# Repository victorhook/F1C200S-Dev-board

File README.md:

# F1C200S Dev Board

Custom PCB with the Allwinner F1C200S SoC, built to learn more about embedded Linux!

## Overview

The F1C200S is an ARM9 (ARM926EJ-S) processor with 64MB DDR1 RAM built into the package.
No external memory needed -- a 2-layer PCB is all it takes to run Linux.

## Features

- **SoC**: Allwinner F1C200S (ARM9 @ 408MHz, 64MB SiP DDR1)
- **Boot**: Micro SD card
- **USB**: USB-C (OTG + FEL mode flashing)
- **Debug**: UART0 console header, RESET and BOOT/FEL buttons
- **Power**: 5V USB input, 3x LDO regulators (3.3V, 2.5V, 1.2V)
- **Clock**: 24MHz crystal

## Broken-out peripherals

The board exposes most of the SoC's peripherals via pin headers:

- 3x UART, 3x I2C (TWI), 2x SPI, 2x PWM
- 8-bit parallel camera interface (CSI) on a 2x9 header for OV2640 breakout
- Composite video output (TVOUT)
- Built-in audio codec (headphone out, mic in, line in, FM in)
- IR receiver input
- Two 16-pin 2.54mm headers with misc GPIO and power (Port D and Port E)

## Hardware

- **EDA**: KiCad 9
- **PCB**: 2-layer
- **Assembly**: Designed for JLCPCB SMT assembly

Schematic and board files are in `F1C200S-Dev-board/`.

## Software

The `br2-external/` tree has everything needed to build a bootable SD card image with Buildroot:

- **Linux**: 6.19.11 (suniv/sun8i, custom device tree)
- **U-Boot**: 2025.01 (`licheepi_nano` defconfig + custom DTS)
- **Rootfs**: musl + BusyBox, Dropbear SSH, wpa_supplicant
- **Flashing**: `sunxi-fel` over USB

```sh
make            # clone buildroot + build everything
make kernel     # safe kernel rebuild after DTS / linux patch / fragment changes
make uboot      # safe U-Boot rebuild after U-Boot DTS / patch / config changes
make menuconfig # tweak buildroot config
```

Output: `buildroot/output/images/sdcard.img`

## Common workflows

Use these as the default rules of thumb:

| If you changed... | Rebuild with... | Deploy with... |
| --- | --- | --- |
| `src/**` userspace tools/apps | `make deploy-apps` | included in `make deploy-apps` |
| `br2-external/board/f1c200s-devboard/dts/**` | `make kernel` | `make deploy-kernel` |
| `br2-external/board/f1c200s-devboard/linux-patches/**` | `make kernel` | `make deploy-kernel` |
| `br2-external/board/f1c200s-devboard/linux.fragment` | `make kernel` | `make deploy-kernel` |
| kernel config via `make linux-menuconfig` | `make kernel` | `make deploy-kernel` |
| `br2-external/board/f1c200s-devboard/u-boot*` or U-Boot DTS/patches | `make uboot` | no network deploy target; reflash boot media |
| Buildroot defconfig / package selection | `make defconfig && make` | depends on what changed |

Notes:

- `make deploy-kernel` only installs `zImage` and `suniv-f1c200s-devboard.dtb`
  to the boot partition on the running board.
- `make deploy-apps` rebuilds and copies the userspace binaries under `src/`
  plus selected target tools like `yavta`.
- There is intentionally no `make image` target anymore. It was too fragile for
  kernel patch stack changes.

## Status

Rev A -- initial prototype

**2026-04-20**: First Linux boot! Rev A boards arrived and reached a busybox root shell
on UART0. The core path (USB-C power, DDR1, 24MHz PLL, MMC, pinctrl, UART, GPIO LEDs,
SPI) is all verified working under Linux 6.19.11. Later the same day, USB composite
gadget (CDC ECM ethernet + CDC ACM serial) came up — one USB-C cable now carries
power, a shell on `/dev/ttyACM0`, and a network link on `usb0` (192.168.100.1).
Buttons work via the input subsystem (`/dev/input/event0`) after a kernel patch
that aligns suniv's pinctrl strict-mode behaviour with other sunxi SoCs.

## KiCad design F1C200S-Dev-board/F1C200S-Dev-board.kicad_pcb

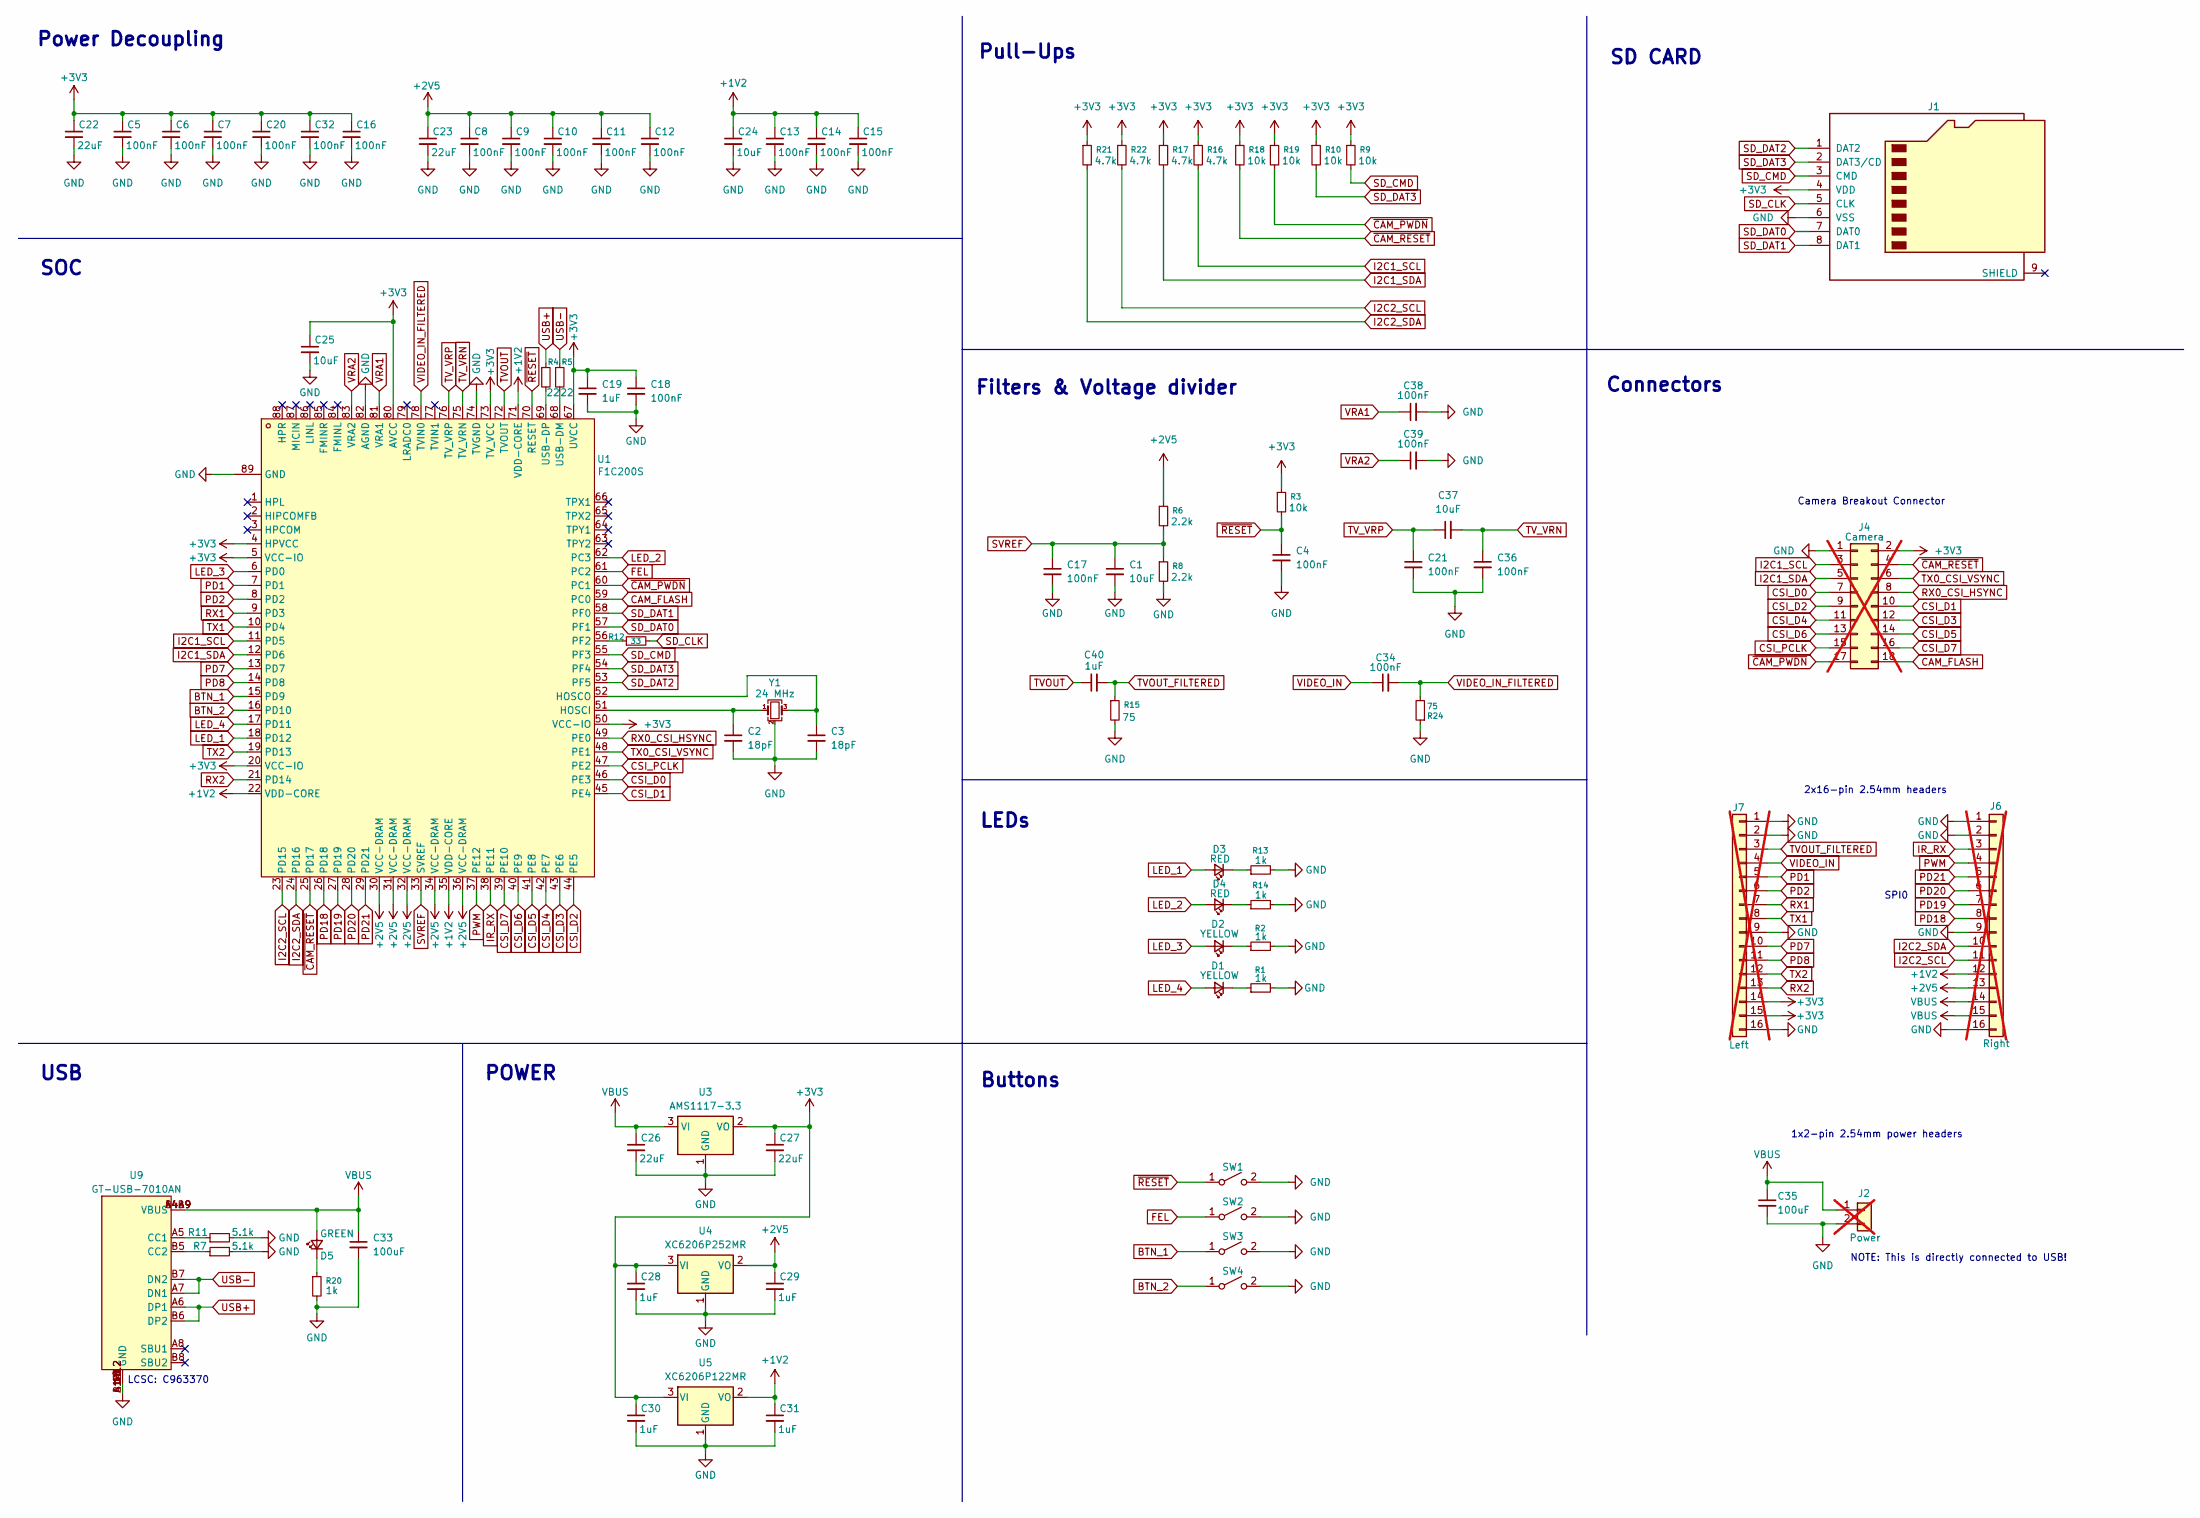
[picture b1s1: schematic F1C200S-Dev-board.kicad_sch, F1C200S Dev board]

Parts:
C1, C24, C25: 10uF; C_0603_1608Metric
C2, C3: 18pF; C_0402_1005Metric; LCSC Part C1549
C4, C5, C6, C7, C8, C9, C10, C11, C12, C13, C14, C15, C16, C17, C18, C20, C21, C32, C34, C36, C38, C39: 100nF; C_0402_1005Metric
C19, C40: 1uF; C_0402_1005Metric
C22, C23, C26, C27: 22uF; C_0603_1608Metric
C28, C29, C30, C31: 1uF; C_0603_1608Metric
C33, C35: 100uF; C_1206_3216Metric; LCSC Part C15008
C37: 10uF; C_0402_1005Metric
D1, D2: YELLOW; LED_0603_1608Metric; LCSC Part C2290
D3, D4: RED; LED_0603_1608Metric; LCSC Part C2286
D5: GREEN; LED_0805_2012Metric; LCSC Part C2297
J1: Micro_SD_Card; TF-SMD_TF-021B-H265; LCSC Part C498185
J2: Power; PinSocket_1x02_P2.54mm_Vertical; not fitted
J4: Camera; PinSocket_2x09_P2.54mm_Vertical; not fitted
J6: Right; PinSocket_1x16_P2.54mm_Vertical; not fitted
J7: Left; PinSocket_1x16_P2.54mm_Vertical; not fitted
R1, R2, R13, R14, R20: 1k; R_0402_1005Metric
R3, R9, R10, R18, R19: 10k; R_0402_1005Metric
R4, R5: 22; R_0402_1005Metric; LCSC Part C25092
R6, R8: 2.2k; R_0402_1005Metric
R7, R11: 5.1k; R_0402_1005Metric
R12: 33; R_0402_1005Metric; LCSC Part C25105
R15, R24: 75; R_0603_1608Metric; LCSC Part C4275
R16, R17, R21, R22: 4.7k; R_0402_1005Metric
SW1, SW2, SW3, SW4: SW_SPST; SW-SMD_L3.9-W3.0-P4.45; LCSC Part C720477
U1: F1C200S; QFN-88_L10.0-W10.0-P0.40-BL-EP6.75; LCSC Part C2879851
U3: AMS1117-3.3; SOT-223-3_TabPin2; LCSC Part C6186
U4: XC6206P252MR; SOT-23-3; LCSC Part C15906
U5: XC6206P122MR; SOT-23-3; LCSC Part C424699
U9: GT-USB-7010AN; USB-SMD_GT-USB-7010AN; LCSC Part C963370
Y1: 24 MHz; Crystal_SMD_3225-4Pin_3.2x2.5mm; LCSC Part C37635376

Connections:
+1V2: C13.1, C14.1, C15.1, C24.1, C31.1, J6.12, U1.22 (VDD-CORE), U1.35 (VDD-CORE), U1.71 (VDD-CORE), U5.2 (VO)
+2V5: C8.1, C9.1, C10.1, C11.1, C12.1, C23.1, C29.1, J6.13, R6.1, U1.30 (VCC-DRAM), U1.31 (VCC-DRAM), U1.32 (VCC-DRAM), U1.34 (VCC-DRAM), U1.36 (VCC-DRAM), U4.2 (VO)
+3V3: C5.1, C6.1, C7.1, C16.1, C18.1, C19.1, C20.1, C22.1, C25.1, C27.1, C28.1, C30.1, C32.1, J1.4 (VDD), J4.2, J7.14, J7.15, R3.1, R9.1, R10.1, R16.1, R17.1, R18.1, R19.1, R21.1, R22.1, U1.4 (HPVCC), U1.5 (VCC-IO), U1.20 (VCC-IO), U1.50 (VCC-IO), U1.67 (UVCC), U1.73 (TV_VCC), U1.80 (AVCC), U3.2 (VO), U4.3 (VI), U5.3 (VI)
BTN_1: SW3.1 (A), U1.15 (PD9)
BTN_2: SW4.1 (A), U1.16 (PD10)
CAM_FLASH: J4.18, U1.59 (PC0)
CSI_D0: J4.7, U1.46 (PE3)
CSI_D1: J4.10, U1.45 (PE4)
CSI_D2: J4.9, U1.44 (PE5)
CSI_D3: J4.12, U1.43 (PE6)
CSI_D4: J4.11, U1.42 (PE7)
CSI_D5: J4.14, U1.41 (PE8)
CSI_D6: J4.13, U1.40 (PE9)
CSI_D7: J4.16, U1.39 (PE10)
CSI_PCLK: J4.15, U1.47 (PE2)
FEL: SW2.1 (A), U1.61 (PC2)
GND: C1.2, C2.2, C3.2, C4.2, C5.2, C6.2, C7.2, C8.2, C9.2, C10.2, C11.2, C12.2, C13.2, C14.2, C15.2, C16.2, C17.2, C18.2, C19.2, C20.2, C21.2, C22.2, C23.2, C24.2, C25.2, C26.2, C27.2, C28.2, C29.2, C30.2, C31.2, C32.2, C33.2, C35.2, C36.2, C38.2, C39.2, J1.6 (VSS), J2.2, J4.1, J6.1, J6.2, J6.9, J6.16, J7.1, J7.2, J7.9, J7.16, R1.2, R2.2, R7.2, R8.2, R11.2, R13.2, R14.2, R15.2, R20.2, R24.1, SW1.2 (B), SW2.2 (B), SW3.2 (B), SW4.2 (B), U1.74 (TVGND), U1.82 (AGND), U1.89 (GND), U3.1 (GND), U4.1 (GND), U5.1 (GND), U9.13 (GND), U9.14 (GND), U9.15 (GND), U9.16 (GND), U9.A1B12 (GND), U9.B1A12 (GND), Y1.2 (G), Y1.4 (G)
I2C1_SCL: J4.3, R16.2, U1.11 (PD5)
I2C1_SDA: J4.5, R17.2, U1.12 (PD6)
I2C2_SCL: J6.11, R22.2, U1.23 (PD15)
I2C2_SDA: J6.10, R21.2, U1.24 (PD16)
IR_RX: J6.3, U1.38 (PE11)
LED_1: D3.2 (A), U1.18 (PD12)
LED_2: D4.2 (A), U1.62 (PC3)
LED_3: D2.2 (A), U1.6 (PD0)
LED_4: D1.2 (A), U1.17 (PD11)
unnamed: D1.1 (K), R1.1
unnamed: D2.1 (K), R2.1
unnamed: D3.1 (K), R13.1
unnamed: D4.1 (K), R14.1
unnamed: D5.1 (K), R20.1
unnamed: C2.1, U1.51 (HOSCI), Y1.1
unnamed: C3.1, U1.52 (HOSCO), Y1.3
unnamed: R12.1, U1.56 (PF2)
unnamed: R5.2, U1.68 (USB-DM)
unnamed: R4.2, U1.69 (USB-DP)
unnamed: R11.1, U9.A5 (CC1)
unnamed: R7.1, U9.B5 (CC2)
PD1: J7.5, U1.7 (PD1)
PD2: J7.6, U1.8 (PD2)
PD7: J7.10, U1.13 (PD7)
PD8: J7.11, U1.14 (PD8)
PD18: J6.8, U1.26 (PD18)
PD19: J6.7, U1.27 (PD19)
PD20: J6.6, U1.28 (PD20)
PD21: J6.5, U1.29 (PD21)
PWM: J6.4, U1.37 (PE12)
RX0_CSI_HSYNC: J4.8, U1.49 (PE0)
RX1: J7.7, U1.9 (PD3)
RX2: J7.13, U1.21 (PD14)
SD_CLK: J1.5 (CLK), R12.2
SD_CMD: J1.3 (CMD), R9.2, U1.55 (PF3)
SD_DAT0: J1.7 (DAT0), U1.57 (PF1)
SD_DAT1: J1.8 (DAT1), U1.58 (PF0)
SD_DAT2: J1.1 (DAT2), U1.53 (PF5)
SD_DAT3: J1.2 (DAT3/CD), R10.2, U1.54 (PF4)
SVREF: C1.1, C17.1, R6.2, R8.1, U1.33 (SVREF)
TVOUT: C40.1, U1.72 (TVOUT)
TVOUT_FILTERED: C40.2, J7.3, R15.1
TV_VRN: C36.1, C37.2, U1.75 (TV_VRN)
TV_VRP: C21.1, C37.1, U1.76 (TV_VRP)
TX0_CSI_VSYNC: J4.6, U1.48 (PE1)
TX1: J7.8, U1.10 (PD4)
TX2: J7.12, U1.19 (PD13)
USB+: R4.1, U9.A6 (DP1), U9.B6 (DP2)
USB-: R5.1, U9.A7 (DN1), U9.B7 (DN2)
VBUS: C26.1, C33.1, C35.1, D5.2 (A), J2.1, J6.14, J6.15, U3.3 (VI), U9.A4B9 (VBUS), U9.B4A9 (VBUS)
VIDEO_IN: C34.1, J7.4
VIDEO_IN_FILTERED: C34.2, R24.2, U1.78 (TVIN0)
VRA1: C38.1, U1.81 (VRA1)
VRA2: C39.1, U1.83 (VRA2)
~CAM_PWDN: J4.17, R19.2, U1.60 (PC1)
~CAM_RESET: J4.4, R18.2, U1.25 (PD17)
~RESET: C4.1, R3.2, SW1.1 (A), U1.70 (RESET)

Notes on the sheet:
Power Decoupling
2x16-pin 2.54mm headers
Connectors
Buttons
Filters & Voltage divider
SD CARD
1x2-pin 2.54mm power headers
LEDs
SOC
Pull-Ups
USB
Camera Breakout Connector
NOTE: This is directly connected to USB!
SPI0
LCSC: C963370
POWER

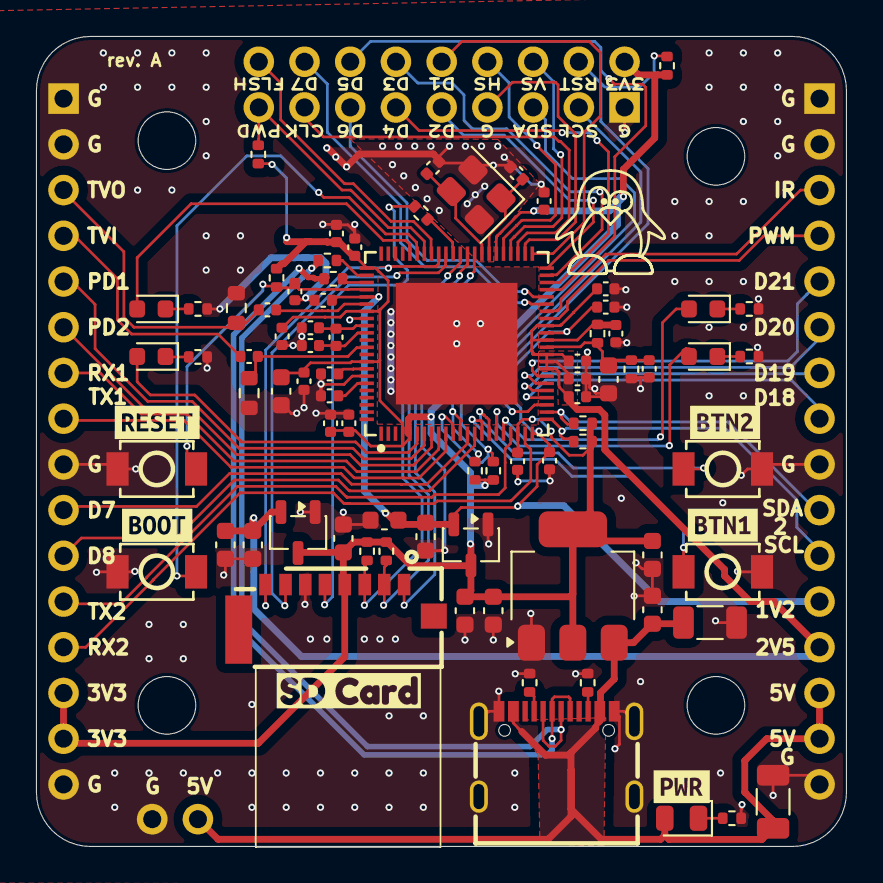
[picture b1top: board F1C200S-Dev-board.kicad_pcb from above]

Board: 2 copper layers, 45.0 x 45.0 mm, 89 parts (0 on the bottom side), 74 nets.

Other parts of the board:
kibuzzard-67EE0EFE: G***; kibuzzard-67EE0EFE
kibuzzard-69D20BF5: G***; kibuzzard-69D20BF5
kibuzzard-69D21EBA: G***; kibuzzard-69D21EBA
kibuzzard-69D21EC5: G***; kibuzzard-69D21EC5
kibuzzard-69D21F31: G***; kibuzzard-69D21F31
kibuzzard-69D21F51: G***; kibuzzard-69D21F51

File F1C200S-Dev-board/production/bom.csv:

Designator,Footprint,Quantity,Value,LCSC Part #
"C1, C24, C25",0603,3,10uF,
"C10, C11, C12, C13, C14, C15, C16, C17, C18, C20, C21, C32, C34, C36, C38, C39, C4, C5, C6, C7, C8, C9",0402,22,100nF,
"C19, C40",0402,2,1uF,
"C2, C3",0402,2,18pF,C1549
"C22, C23, C26, C27",0603,4,22uF,
"C28, C29, C30, C31",0603,4,1uF,
"C33, C35",1206,2,100uF,C15008
C37,0402,1,10uF,
"D1, D2",0603,2,YELLOW,C2290
"D3, D4",0603,2,RED,C2286
D5,0805,1,GREEN,C2297
J1,TF-SMD_TF-021B-H265,1,Micro_SD_Card,C498185
"R1, R13, R14, R2, R20",0402,5,1k,
"R10, R18, R19, R3, R9",0402,5,10k,
"R11, R7",0402,2,5.1k,
R12,0402,1,33,C25105
"R15, R24",0603,2,75,C4275
"R16, R17, R21, R22",0402,4,4.7k,
"R4, R5",0402,2,22,C25092
"R6, R8",0402,2,2.2k,
"SW1, SW2, SW3, SW4",SW-SMD_L3.9-W3.0-P4.45,4,SW_SPST,C720477
U1,QFN-88_L10.0-W10.0-P0.40-BL-EP6.75,1,F1C200S,C2879851
U3,SOT-223-3_TabPin2,1,AMS1117-3.3,C6186
U4,SOT-23-3,1,XC6206P252MR,C15906
U5,SOT-23-3,1,XC6206P122MR,C424699
U9,USB-SMD_GT-USB-7010AN,1,GT-USB-7010AN,C963370
Y1,Crystal_SMD_3225-4Pin_3.2x2.5mm,1,24 MHz,C37635376

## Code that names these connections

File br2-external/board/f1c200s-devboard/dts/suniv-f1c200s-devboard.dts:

// SPDX-License-Identifier: (GPL-2.0+ OR MIT)
// Device tree for F1C200S Dev Board Rev A
// Linux kernel version (include path relative to arch/arm/boot/dts/)

/dts-v1/;
#include "allwinner/suniv-f1c100s.dtsi"
#include <dt-bindings/clock/suniv-ccu-f1c100s.h>
#include <dt-bindings/reset/suniv-ccu-f1c100s.h>
#include <dt-bindings/gpio/gpio.h>
#include <dt-bindings/input/input.h>

/ {
	model = "F1C200S Dev Board";
	compatible = "custom,f1c200s-devboard",
		     "allwinner,suniv-f1c200s",
		     "allwinner,suniv-f1c100s";

	aliases {
		mmc0 = &mmc0;
		serial0 = &uart0;
		serial1 = &uart1;
	};

	chosen {
		stdout-path = "serial0:115200n8";
	};

	memory@80000000 {
		device_type = "memory";
		reg = <0x80000000 0x04000000>; /* 64 MB */
	};

	reg_vcc3v3: reg-vcc3v3 {
		compatible = "regulator-fixed";
		regulator-name = "vcc3v3";
		regulator-min-microvolt = <3300000>;
		regulator-max-microvolt = <3300000>;
	};

	leds {
		compatible = "gpio-leds";

		led1 {
			label = "devboard:led1";
			gpios = <&pio 3 12 GPIO_ACTIVE_HIGH>; /* PD12 */
			linux,default-trigger = "heartbeat";
		};

		led2 {
			label = "devboard:led2";
			gpios = <&pio 2 3 GPIO_ACTIVE_HIGH>; /* PC3 */
		};

		led3 {
			label = "devboard:led3";
			gpios = <&pio 3 0 GPIO_ACTIVE_HIGH>; /* PD0 */
		};

		led4 {
			label = "devboard:led4";
			gpios = <&pio 3 11 GPIO_ACTIVE_HIGH>; /* PD11 */
			linux,default-trigger = "mmc0";
		};
	};

	gpio-keys {
		compatible = "gpio-keys";
		pinctrl-names = "default";
		pinctrl-0 = <&button1_pd9_pin>, <&button2_pd10_pin>;

		button-1 {
			label = "User Button 1";
			linux,code = <KEY_ENTER>;
			gpios = <&pio 3 9 GPIO_ACTIVE_LOW>; /* PD9 */
		};

		button-2 {
			label = "User Button 2";
			linux,code = <KEY_ESC>;
			gpios = <&pio 3 10 GPIO_ACTIVE_LOW>; /* PD10 */
		};
	};

	/*
	 * TVOUT - Composite video output on TVOUT pin (pin 72)
	 * The display pipeline nodes (fe0, be0, tcon0) are not yet in
	 * mainline suniv-f1c100s.dtsi. Once upstreamed, enable with:
	 *   &fe0   { status = "okay"; };
	 *   &be0   { status = "okay"; };
	 *   &tcon0 { status = "okay"; };
	 *
	 * TVIN - Composite video input on TVIN0/TVIN1 pins (pins 78/77)
	 * Requires V4L2 driver for suniv TV decoder (not in mainline).
	 */

	/* Dummy 24 MHz clock handed to the OV2640 driver as "xvclk".
	 * The camera module has its own onboard crystal; the driver
	 * just needs a clk phandle it can call clk_prepare_enable() on.
	 * fixed-clock makes that a no-op.
	 */
	ov2640_xvclk: ov2640-xvclk {
		compatible = "fixed-clock";
		#clock-cells = <0>;
		clock-frequency = <24000000>;
	};
};

/* Nodes not in mainline suniv dtsi yet - define inline */
&{/soc} {
	uart1: serial@1c25400 {
		compatible = "snps,dw-apb-uart";
		reg = <0x01c25400 0x400>;
		interrupts = <2>;
		reg-shift = <2>;
		reg-io-width = <4>;
		clocks = <&ccu CLK_BUS_UART1>;
		resets = <&ccu RST_BUS_UART1>;
		pinctrl-names = "default";
		pinctrl-0 = <&uart1_pd_pins>;
		status = "okay";
	};

	/* CSI (parallel camera interface).
	 *
	 * Requires the sun4i-csi suniv compatible patch under linux-patches/.
	 *
	 * Pin conflict with UART0 console: PE0/PE1 carry CSI HSYNC/VSYNC
	 * but are also the UART0 TX/RX console pins. When you enable CSI
	 * (status = "okay" below), either:
	 *   a) set status = "disabled" on &uart0, and switch the console
	 *      to /dev/ttyGS0 (USB gadget, already set up in rcS), OR
	 *   b) accept that the serial console goes silent while camera runs.
	 *
	 * IRQ 24 is best-guess for CSI on suniv; verify against the F1C100S
	 * datasheet interrupt table before trusting it in production.
	 */
	csi0: csi@1cb0000 {
		compatible = "allwinner,suniv-f1c100s-csi";
		reg = <0x01cb0000 0x1000>;
		interrupts = <32>;
		clocks = <&ccu CLK_BUS_CSI>, <&ccu CLK_DRAM_CSI>;
		clock-names = "bus", "ram";
		resets = <&ccu RST_BUS_CSI>;
		pinctrl-names = "default";
		pinctrl-0 = <&csi_pe_pins>;
		status = "okay";

		/* Run CSI in RAW passthrough mode: sun4i-csi will expose a
		 * single-plane VIDEO_CAPTURE device (YUYV / UYVY) instead of
		 * the default multi-plane YUV420M.  Needed because the
		 * YUV422->YUV420 planar conversion hardware on suniv is
		 * broken (captures ~1/4 of bytes per row). */
		packed-format;

		port {
			csi_in: endpoint {
				remote-endpoint = <&ov2640_out>;
				bus-width = <8>;
				/* hsync-active=<0> and vsync-active=<0> here
				 * become HREF_POL=1 / VREF_POL=1 in the CSI
				 * hardware register (sun4i-csi inverts the
				 * HSYNC/HREF polarity semantics — see the
				 * comment in sun4i_dma.c around the CFG write).
				 * That matches what our bare-metal csi-capture
				 * tool uses, which was proven to work.
				 * OV2640 drives HREF/VSYNC active-high. */
				hsync-active = <0>;
				vsync-active = <0>;
				pclk-sample = <1>;
			};
		};
	};
};

&pio {
	vcc-pc-supply = <&reg_vcc3v3>;
	vcc-pd-supply = <&reg_vcc3v3>;
	vcc-pe-supply = <&reg_vcc3v3>;
	vcc-pf-supply = <&reg_vcc3v3>;

	uart1_pd_pins: uart1-pd-pins {
		pins = "PD3", "PD4";
		function = "uart1";
	};

	spi0_pd_pins: spi0-pd-pins {
		pins = "PD18", "PD19", "PD20", "PD21";
		function = "spi0";
	};

	ir_rx_pins: ir-rx-pins {
		pins = "PE11";
		function = "ir";
	};

	button1_pd9_pin: button1-pd9-pin {
		pins = "PD9";
		function = "gpio_in";
		bias-pull-up;
	};

	button2_pd10_pin: button2-pd10-pin {
		pins = "PD10";
		function = "gpio_in";
		bias-pull-up;
	};

	/* CSI DVP: PE0=HSYNC, PE1=VSYNC, PE2=PCLK, PE3-PE10=D0-D7 */
	csi_pe_pins: csi-pe-pins {
		pins = "PE0", "PE1", "PE2", "PE3", "PE4",
		       "PE5", "PE6", "PE7", "PE8", "PE9", "PE10";
		function = "csi";
	};

	/* SCCB for OV2640 sensor (I2C1 on PD5/PD6 per board schematic) */
	i2c1_pd_pins: i2c1-pd-pins {
		pins = "PD5", "PD6";
		function = "i2c1";
	};
};

/* UART0 on PE0/PE1 — shares pins with CSI HSYNC/VSYNC.
 * When activating the camera stack, flip this to "disabled" and enable
 * &csi0 + &i2c1 — console moves to /dev/ttyGS0 over USB gadget.
 */
&uart0 {
	pinctrl-names = "default";
	pinctrl-0 = <&uart0_pe_pins>;
	status = "disabled";
};

/* SD card on SDC0 (PF0-PF5) - boot device */
&mmc0 {
	vmmc-supply = <&reg_vcc3v3>;
	bus-width = <4>;
	no-1-8-v;     /* SD card at 3.3V only; we don't support UHS-I signaling */
	broken-cd;    /* no card-detect pin wired */
	disable-wp;   /* no write-protect pin wired */
	status = "okay";
};

&otg_sram {
	status = "okay";
};

&usb_otg {
	dr_mode = "peripheral";
	status = "okay";
};

&usbphy {
	status = "okay";
};

/* SPI0 on PD18-PD21 (mux 4) - wired to display header */
&spi0 {
	pinctrl-names = "default";
	pinctrl-0 = <&spi0_pd_pins>;
	status = "okay";

	/* ST7735R TFT display
	 * SPI: CS=PD18, MOSI=PD19, CLK=PD20, MISO=PD21
	 * DC and reset on PD7/PD8 - adjust to match your wiring.
	 * If you see garbled pixels, try dropping spi-max-frequency to 16 MHz.
	 */
	display@0 {
		compatible = "jianda,jd-t18003-t01";
		reg = <0>;
		spi-max-frequency = <32000000>;
		dc-gpios = <&pio 3 7 GPIO_ACTIVE_HIGH>;    /* PD7 */
		/* This module has an inverter on RST (or clone wiring) — the chip's
		 * reset is physically active-high from the header's point of view.
		 * Using GPIO_ACTIVE_LOW leaves the display permanently reset (white).
		 */
		reset-gpios = <&pio 3 8 GPIO_ACTIVE_HIGH>;  /* PD8 */
		rotation = <0>;
		status = "okay";
	};
};

/* IR receiver on PE3 (directly accessible on header) */
/*
 * NOTE: The suniv IR controller node may not be in the mainline dtsi.
 * If missing, it can be defined similarly to uart1 above at address
 * 0x01c22c00. The IR_RX pin is routed to the board headers.
 */

/* I2C1 = SCCB bus for OV2640. Enabled alongside &csi0 for camera use. */
&i2c1 {
	pinctrl-names = "default";
	pinctrl-0 = <&i2c1_pd_pins>;
	clock-frequency = <100000>;
	status = "okay";

	ov2640: camera@30 {
		compatible = "ovti,ov2640";
		reg = <0x30>;
		clocks = <&ov2640_xvclk>;
		clock-names = "xvclk";
		/* Net mapping confirmed from schematic:
		 *   CAM_RESET → PD17  (SoC pin 25, active-low)
		 *   CAM_PWDN  → PC1   (active-high, still to be double-checked)
		 * Previous PC2 was actually the FEL net — wrong pin.
		 */
		resetb-gpios = <&pio 3 17 GPIO_ACTIVE_LOW>;
		pwdn-gpios = <&pio 2 1 GPIO_ACTIVE_HIGH>;

		port {
			ov2640_out: endpoint {
				remote-endpoint = <&csi_in>;
				bus-width = <8>;
				/* Must match csi_in polarity — V4L2 requires
				 * endpoint pair to agree. */
				hsync-active = <0>;
				vsync-active = <0>;
				pclk-sample = <1>;
			};
		};
	};
};

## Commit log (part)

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2026-04-20 Added image of first bingup
